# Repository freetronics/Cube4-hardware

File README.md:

Freetronics Cube
===========================
Copyright 2010-2013 Freetronics Pty Ltd  
Freetronics site:  www.freetronics.com  
Freetronics email: info@freetronics.com  

The Cube is a USB powered, smart RGB LED Cube kit, with a serial command
interface for direct control and learning, an open source driver library
and an on-board Arduino compatible MCU running the whole show!

The Cube was designed using the open source KiCad schematic and pcb
design package: http://www.kicad.org

The schematic pages have been carefully laid out to make it easy to follow and
learn about a larger microcontroller based project design in operation.

Features:

 * Power and control by USB commands straight from your computer (Windows, Mac or Linux)
 * Expansion port connector for sensors, joysticks, game and interface add ons
 * Onboard ATmega32u4 MCU (Arduino Leonardo compatible)
 * USB interface for uploading new sketches and sending serial commands
 * Arduino driver library with example programs and animations at:
   https://github.com/freetronics/Cube4
 * Includes ZigBee/XBee headers so you can add a wireless module (not included)
 * Prototyping area with I2C, power and spare pins next to it

More information is available on our product page at:

  http://www.freetronics.com/cube

This project is made up of 3 schematic and pcb project folders.
Each folder within this repository includes a handy copy of the
schematic in PDF format and image(s) of the main pcb.

INSTALLATION
------------
The design is saved as a KiCad project. KiCad PCB design software is
available from www.kicad.org free and open-source. To use
this project download it and place the directories containing these files
into the a folder on your computer. Then open KiCad and navigate to the
*.pro (project) file for each section.

DISTRIBUTION
------------
The specific terms of distribution of this project are governed by the
license referenced below.

LICENSE
-------
Licensed under the TAPR Open Hardware License (www.tapr.org/OHL).
The "license" folder within this repository also contains a copy of
this license in plain text format.

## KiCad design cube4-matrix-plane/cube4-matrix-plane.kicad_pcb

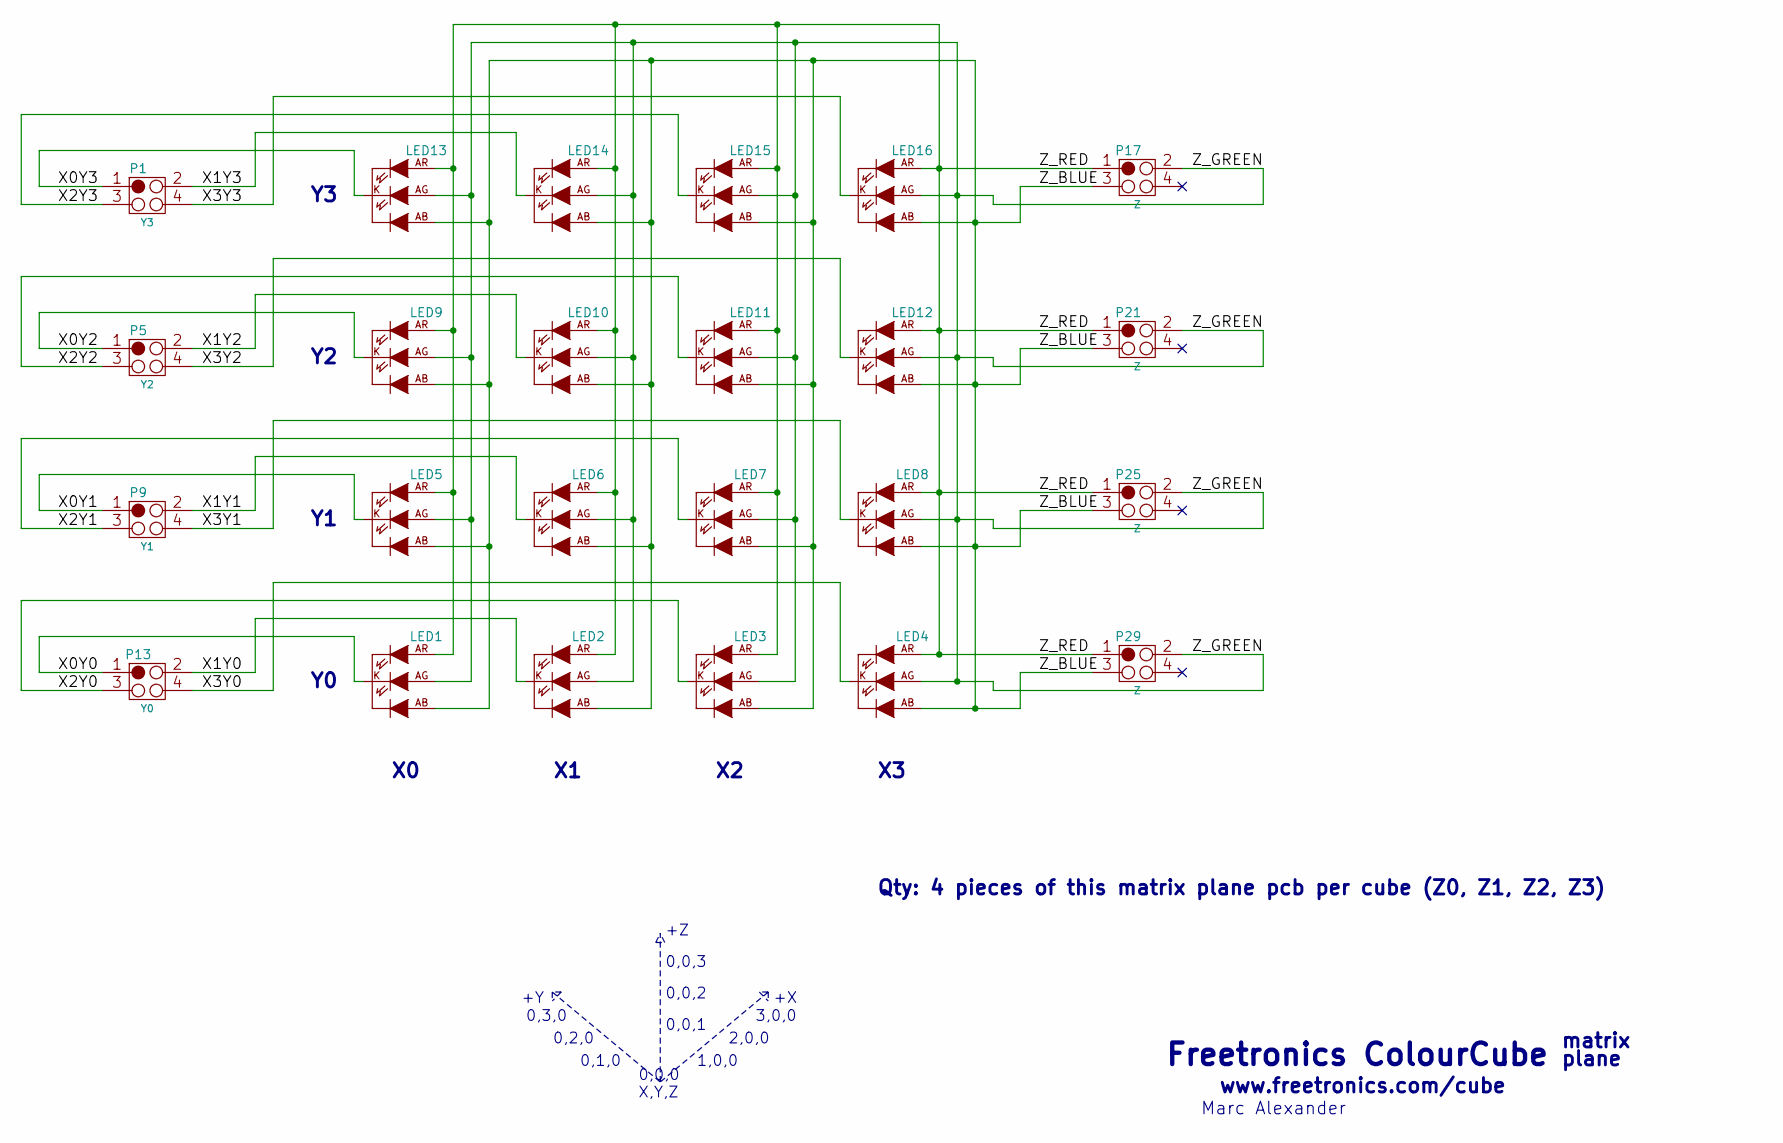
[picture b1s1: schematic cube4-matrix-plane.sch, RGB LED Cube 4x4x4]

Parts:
LED1, LED2, LED3, LED4, LED5, LED6, LED7, LED8, LED9, LED10, LED11, LED12, LED13, LED14, LED15, LED16: LED_RGB_COM_K; LED_RGB_8MM_COM_K
P1: Y3; LED_MATRIX_PLANE_4PAD
P5: Y2; LED_MATRIX_PLANE_4PAD
P9: Y1; LED_MATRIX_PLANE_4PAD
P13: Y0; LED_MATRIX_PLANE_4PAD
P17, P21, P25, P29: Z; LED_MATRIX_PLANE_4PAD

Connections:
/X0Y0: LED1.K, P13.1
/X0Y1: LED5.K, P9.1
/X0Y2: LED9.K, P5.1
/X0Y3: LED13.K, P1.1
/X1Y0: LED2.K, P13.2
/X1Y1: LED6.K, P9.2
/X1Y2: LED10.K, P5.2
/X1Y3: LED14.K, P1.2
/X2Y0: LED3.K, P13.3
/X2Y1: LED7.K, P9.3
/X2Y2: LED11.K, P5.3
/X2Y3: LED15.K, P1.3
/X3Y0: LED4.K, P13.4
/X3Y1: LED8.K, P9.4
/X3Y2: LED12.K, P5.4
/X3Y3: LED16.K, P1.4
/Z_BLUE: LED1.AB, LED2.AB, LED3.AB, LED4.AB, LED5.AB, LED6.AB, LED7.AB, LED8.AB, LED9.AB, LED10.AB, LED11.AB, LED12.AB, LED13.AB, LED14.AB, LED15.AB, LED16.AB, P17.3, P21.3, P25.3, P29.3
/Z_GREEN: LED1.AG, LED2.AG, LED3.AG, LED4.AG, LED5.AG, LED6.AG, LED7.AG, LED8.AG, LED9.AG, LED10.AG, LED11.AG, LED12.AG, LED13.AG, LED14.AG, LED15.AG, LED16.AG, P17.2, P21.2, P25.2, P29.2
/Z_RED: LED1.AR, LED2.AR, LED3.AR, LED4.AR, LED5.AR, LED6.AR, LED7.AR, LED8.AR, LED9.AR, LED10.AR, LED11.AR, LED12.AR, LED13.AR, LED14.AR, LED15.AR, LED16.AR, P17.1, P21.1, P25.1, P29.1

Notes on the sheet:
Qty: 4 pieces of this matrix plane pcb per cube (Z0, Z1, Z2, Z3)
plane
matrix
Marc Alexander
www.freetronics.com/cube
Freetronics ColourCube
0,0,3
0,0,2
0,0,1
0,3,0
0,2,0
0,1,0
3,0,0
2,0,0
1,0,0
0,0,0 X,Y,Z

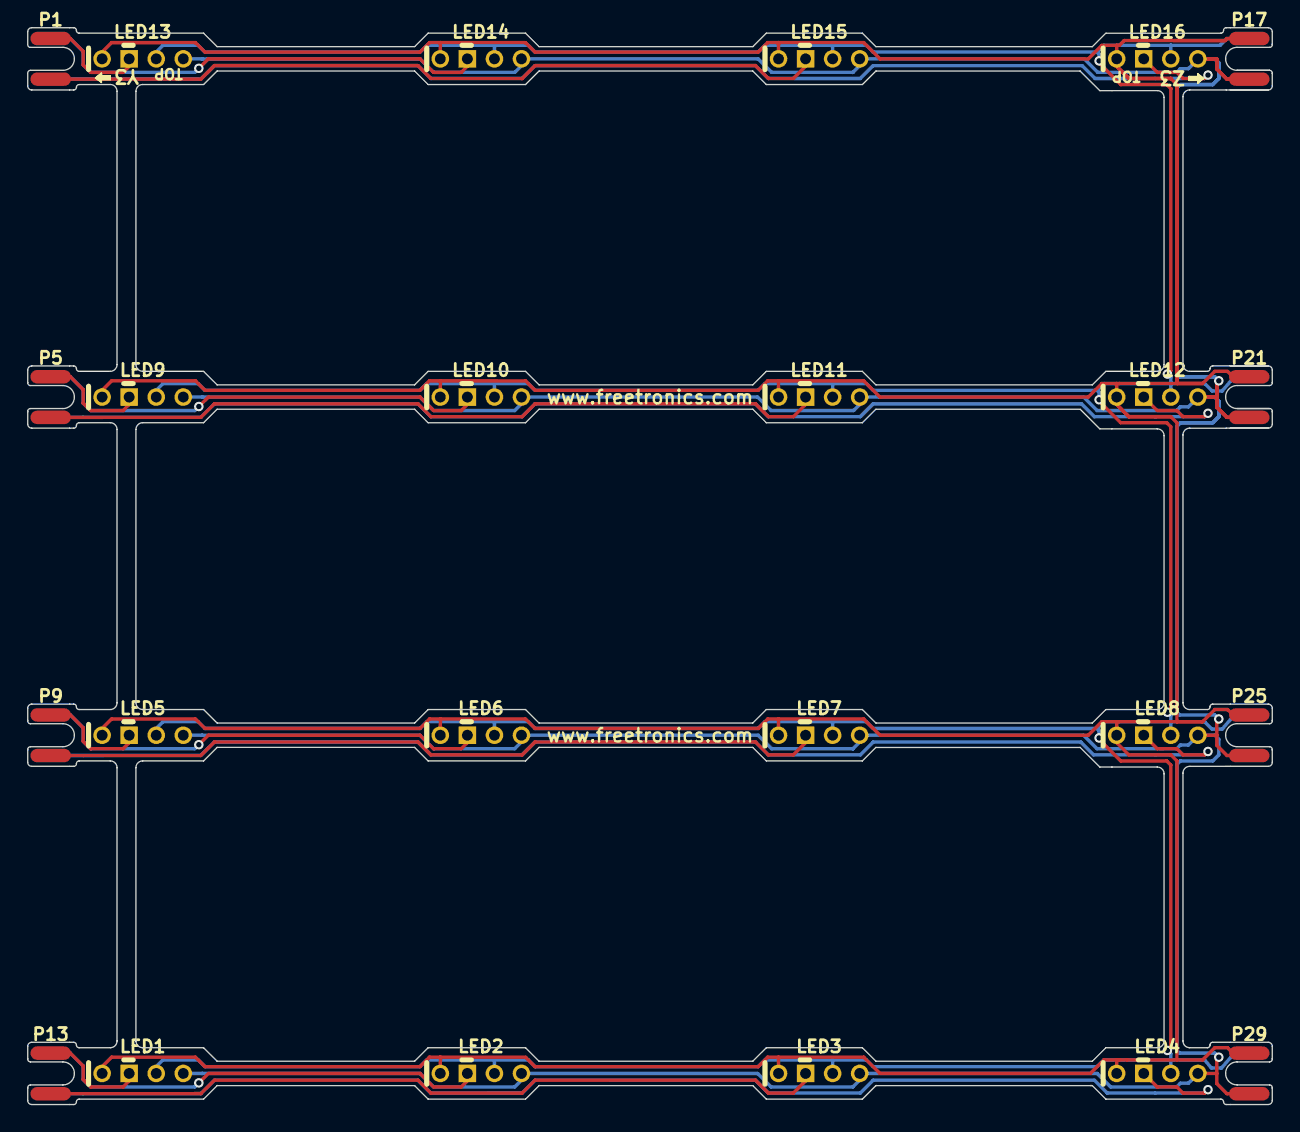
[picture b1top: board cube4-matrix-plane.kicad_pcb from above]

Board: 2 copper layers, 92.0 x 79.6 mm, 24 parts (0 on the bottom side), 19 nets.

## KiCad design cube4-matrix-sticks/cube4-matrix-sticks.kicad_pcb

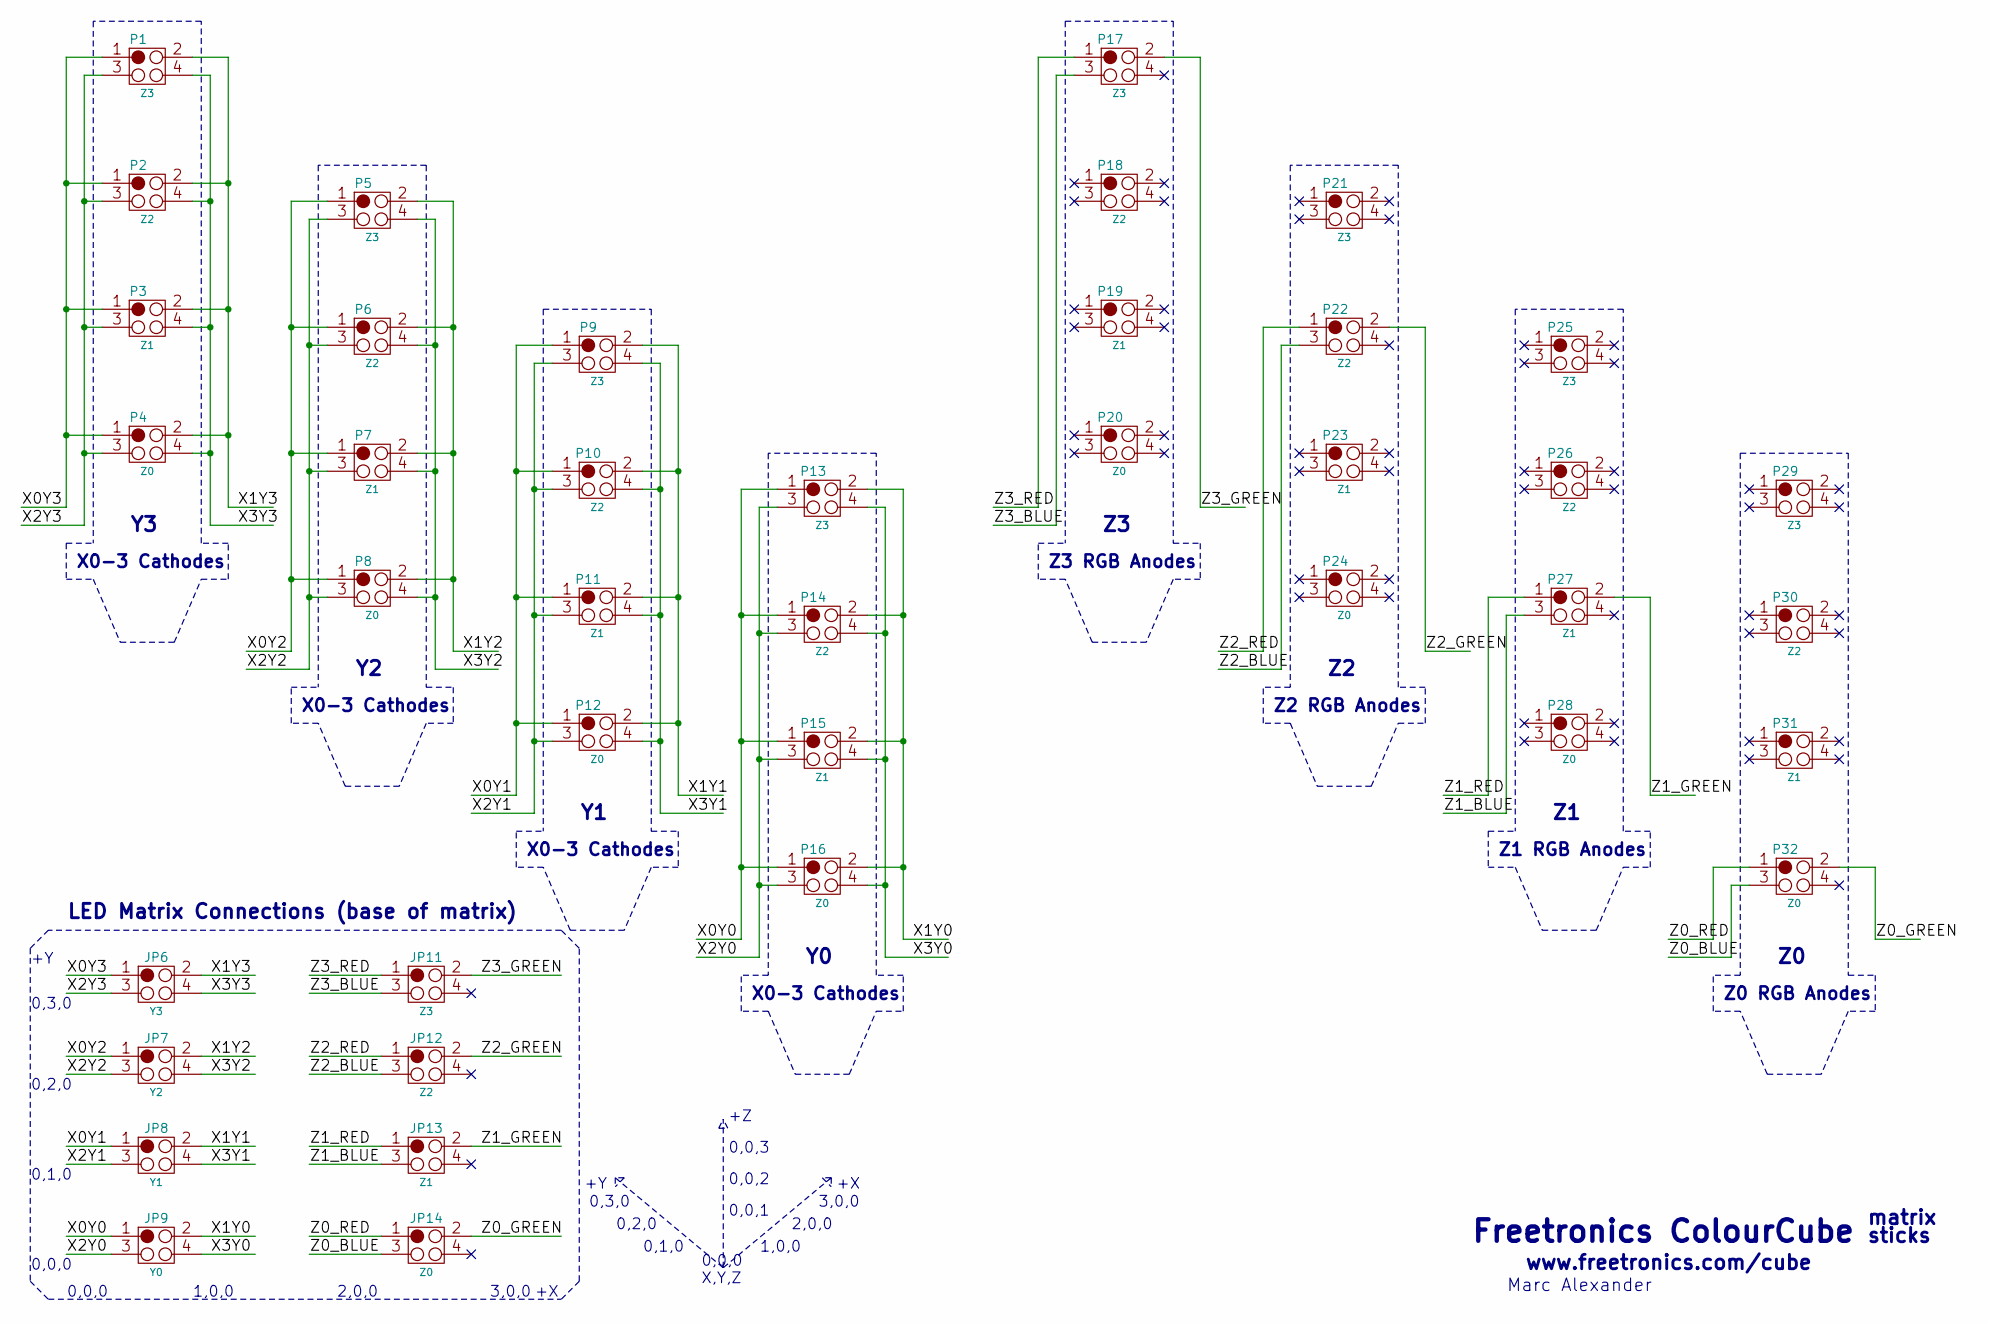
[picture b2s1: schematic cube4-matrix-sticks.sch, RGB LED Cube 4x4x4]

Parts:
JP6: Y3; LED_STICK_BASE_4PAD
JP7: Y2; LED_STICK_BASE_4PAD
JP8: Y1; LED_STICK_BASE_4PAD
JP9: Y0; LED_STICK_BASE_4PAD
JP11: Z3; LED_STICK_BASE_4PAD
JP12: Z2; LED_STICK_BASE_4PAD
JP13: Z1; LED_STICK_BASE_4PAD
JP14: Z0; LED_STICK_BASE_4PAD
P1, P5, P9, P13, P17, P21, P25, P29: Z3; LED_MATRIX_VERTICAL_4PAD
P2, P6, P10, P14, P18, P22, P26, P30: Z2; LED_MATRIX_VERTICAL_4PAD
P3, P7, P11, P15, P19, P23, P27, P31: Z1; LED_MATRIX_VERTICAL_4PAD
P4, P8, P12, P16, P20, P24, P28, P32: Z0; LED_MATRIX_VERTICAL_4PAD

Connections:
/X0Y0: JP9.1, P13.1, P14.1, P15.1, P16.1
/X0Y1: JP8.1, P9.1, P10.1, P11.1, P12.1
/X0Y2: JP7.1, P5.1, P6.1, P7.1, P8.1
/X0Y3: JP6.1, P1.1, P2.1, P3.1, P4.1
/X1Y0: JP9.2, P13.2, P14.2, P15.2, P16.2
/X1Y1: JP8.2, P9.2, P10.2, P11.2, P12.2
/X1Y2: JP7.2, P5.2, P6.2, P7.2, P8.2
/X1Y3: JP6.2, P1.2, P2.2, P3.2, P4.2
/X2Y0: JP9.3, P13.3, P14.3, P15.3, P16.3
/X2Y1: JP8.3, P9.3, P10.3, P11.3, P12.3
/X2Y2: JP7.3, P5.3, P6.3, P7.3, P8.3
/X2Y3: JP6.3, P1.3, P2.3, P3.3, P4.3
/X3Y0: JP9.4, P13.4, P14.4, P15.4, P16.4
/X3Y1: JP8.4, P9.4, P10.4, P11.4, P12.4
/X3Y2: JP7.4, P5.4, P6.4, P7.4, P8.4
/X3Y3: JP6.4, P1.4, P2.4, P3.4, P4.4
/Z0_BLUE: JP14.3, P32.3
/Z0_GREEN: JP14.2, P32.2
/Z0_RED: JP14.1, P32.1
/Z1_BLUE: JP13.3, P27.3
/Z1_GREEN: JP13.2, P27.2
/Z1_RED: JP13.1, P27.1
/Z2_BLUE: JP12.3, P22.3
/Z2_GREEN: JP12.2, P22.2
/Z2_RED: JP12.1, P22.1
/Z3_BLUE: JP11.3, P17.3
/Z3_GREEN: JP11.2, P17.2
/Z3_RED: JP11.1, P17.1

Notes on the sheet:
sticks
Z3 RGB Anodes
Z2 RGB Anodes
Z1 RGB Anodes
Z0 RGB Anodes
X0-3 Cathodes
matrix
Marc Alexander
www.freetronics.com/cube
Freetronics ColourCube
LED Matrix Connections (base of matrix)
0,0,0
0,3,0
0,2,0
0,1,0
3,0,0
2,0,0
1,0,0
0,0,3
0,0,2
0,0,1
0,0,0 X,Y,Z

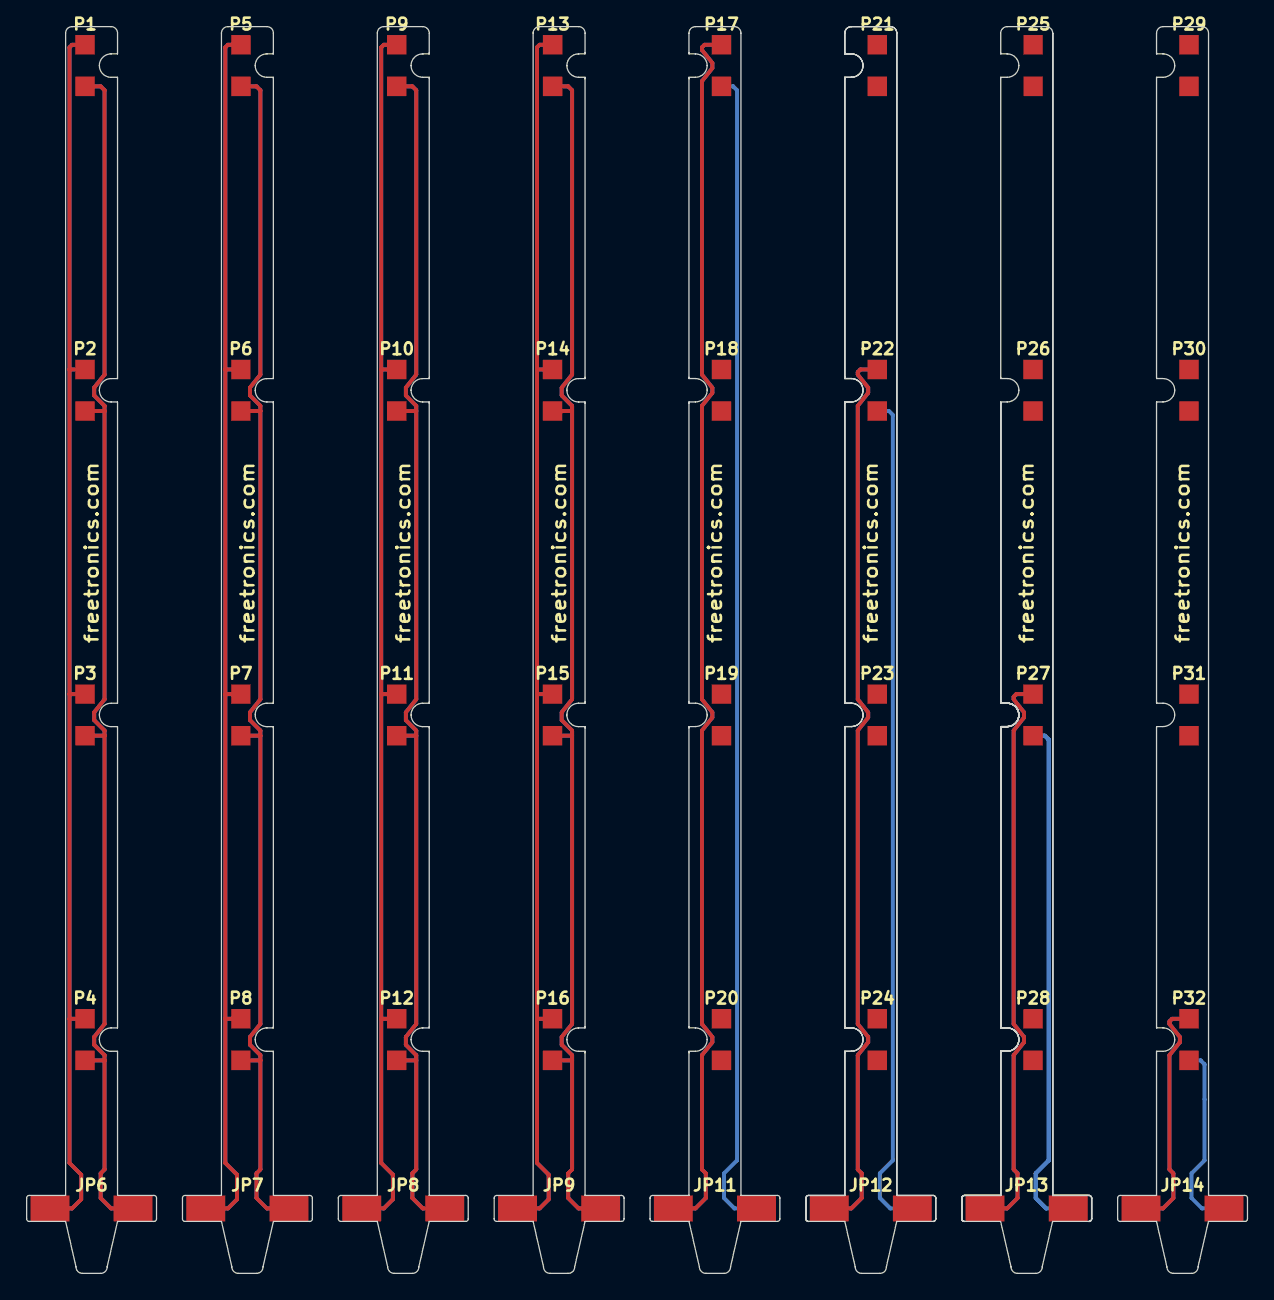
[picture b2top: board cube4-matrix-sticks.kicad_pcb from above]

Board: 2 copper layers, 94.0 x 96.0 mm, 40 parts (0 on the bottom side), 28 nets.

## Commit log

2013-10-03 Cube4 release - July 2012
2014-02-13 Update to Kicad 2013-July, add library as git submodule, add schematic cache files
2021-11-09 Update README.md
    https://forum.kicad.info/t/warning-avoid-all-links-to-kicad-pcb-org-use-kicad-org/31521
